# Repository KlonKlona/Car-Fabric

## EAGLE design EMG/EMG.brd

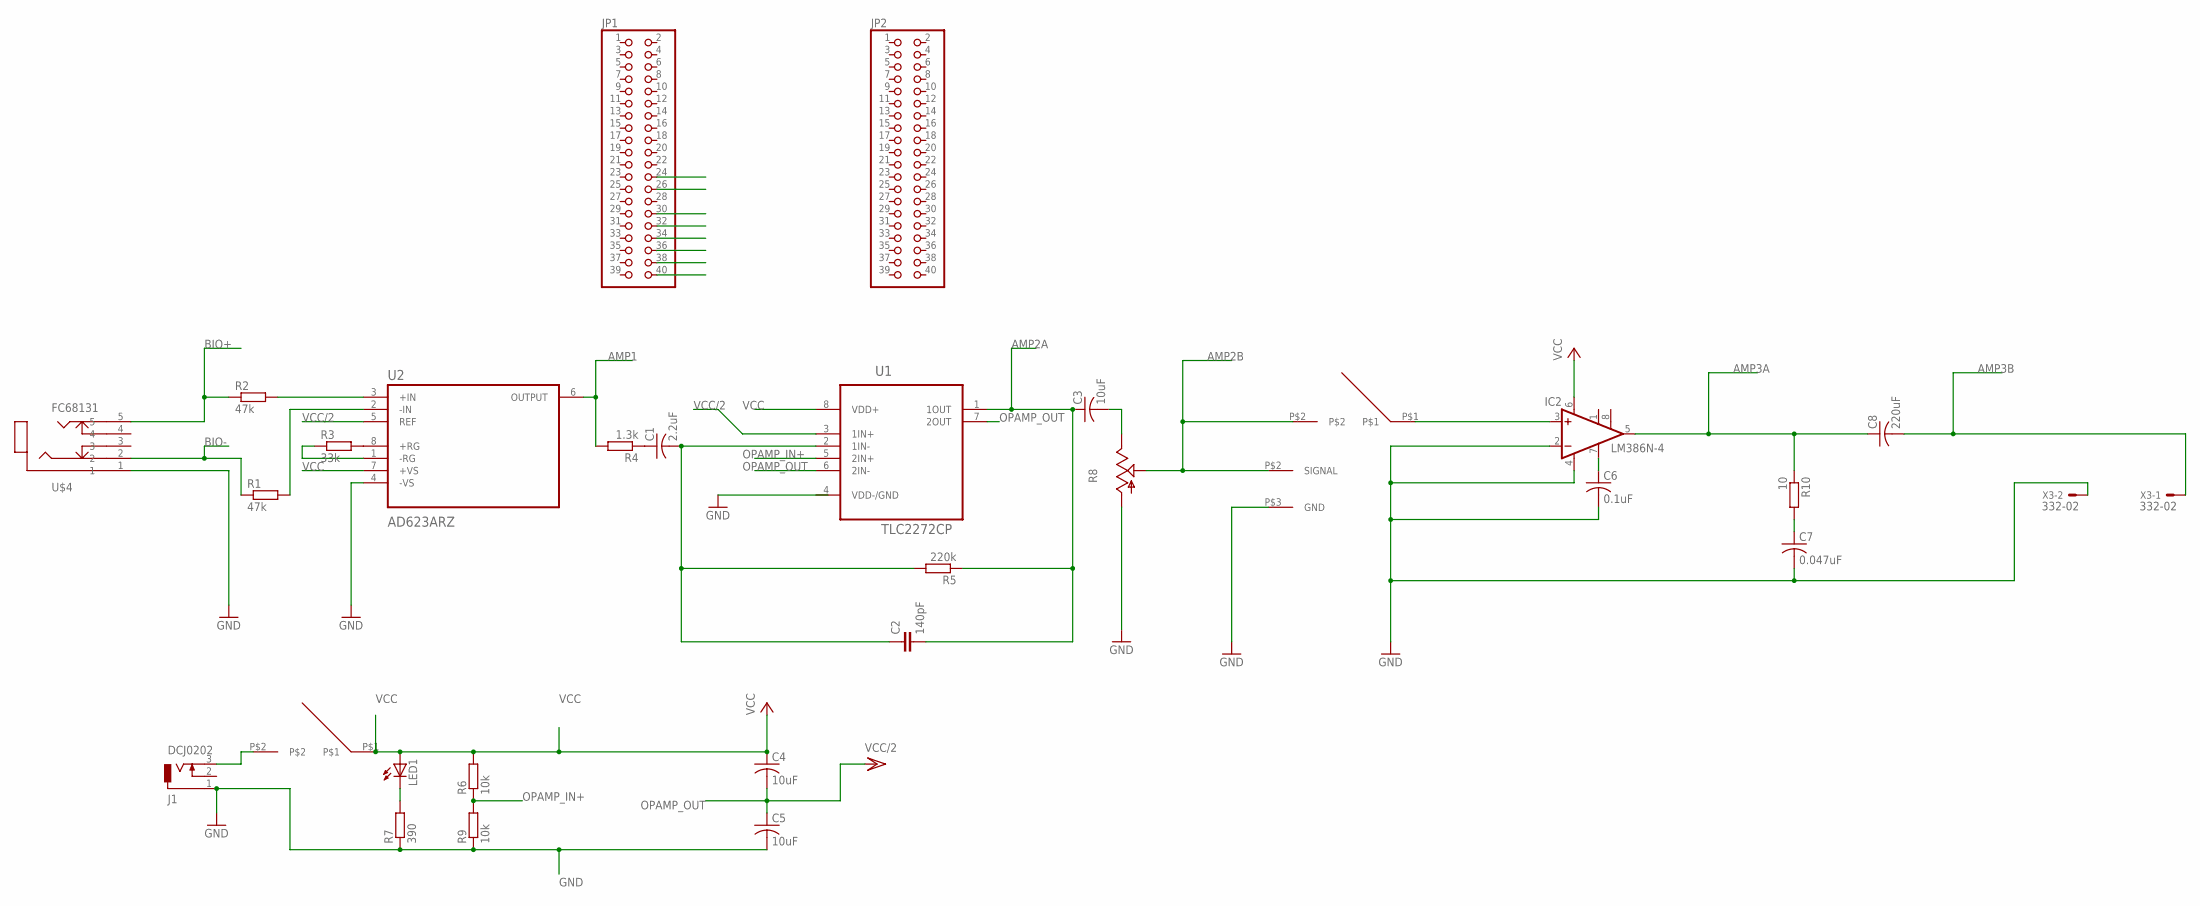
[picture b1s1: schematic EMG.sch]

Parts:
C1: 2.2uF; C025-025X050
C2: 140pF; C7.5B3
C3, C4, C5: 10uF; C025-025X050
C6: 0.1uF; C025-025X050
C7: 0.047uF; C050-030X075
C8: 220uF; C050-030X075
IC2: LM386N-4; DIL08
J1: DCJ0202
JP1, JP2: PINHD-2X20; 2X20
LED1: LED3MM
R1, R2: 47k; 0204/7
R3: 33k; 0204/7
R4: 1.3k; 0204/7
R5: 220k; 0204/7
R6, R9: 10k; 0204/7
R7: 390; 0204/7
R8: TRIM_US-B25U; B25U
R10: 10; 0204/7
U1: TLC2272CP; DIP254P762X508-8
U2: AD623ARZ; SOIC127P600X175-8N
U$1, U$2: CHL-706PG01LWB; PUSH_BUTTON
U$3: 1503_12_JACK_3,5
U$4: FC68131; FC68131-5P
X3: 332-02

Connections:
AMP1: JP1.34, R4.2, U2.6 (OUTPUT)
AMP2A: C2.2, C3.1, JP1.36, R5.1, U1.1 (1OUT)
AMP2B: JP1.38, R8.S, U$2.P$2, U$3.P$2 (SIGNAL)
AMP3A: C8.1, IC2.5 (OUT), R10.1
AMP3B: C8.2, JP1.40, X3.1
BIO+: JP1.32, R2.1, U$4.5
BIO-: JP1.30, R1.1, U$4.2
GND: C5.2, C6.2, C7.2, IC2.2 (-IN), IC2.4 (GND), J1.1, JP1.24, R7.1, R8.A, R9.1, U2.4 (-VS), U$3.P$3 (GND), U$4.1, X3.2
unnamed: R3.2, U2.8 (+RG)
unnamed: R3.1, U2.1 (-RG)
unnamed: R2.2, U2.3 (+IN)
unnamed: R1.2, U2.2 (-IN)
unnamed: C1.1, R4.1
unnamed: J1.3, U$1.P$2
unnamed: C1.2, C2.1, R5.2, U1.2 (1IN-)
unnamed: C3.2, R8.E
unnamed: C6.1, IC2.7 (BYPASS)
unnamed: IC2.3 (+IN), U$2.P$1
unnamed: LED1.K (C), R7.2
unnamed: C7.1, R10.2
OPAMP_IN+: R6.1, R9.2, U1.5 (2IN+)
OPAMP_OUT: C4.2, C5.1, U1.6 (2IN-), U1.7 (2OUT)
VCC: C4.1, IC2.6 (VS), JP1.26, LED1.A, R6.2, U1.8 (VDD+), U2.7 (+VS), U$1.P$1
VCC/2: U1.3 (1IN+), U2.5 (REF)

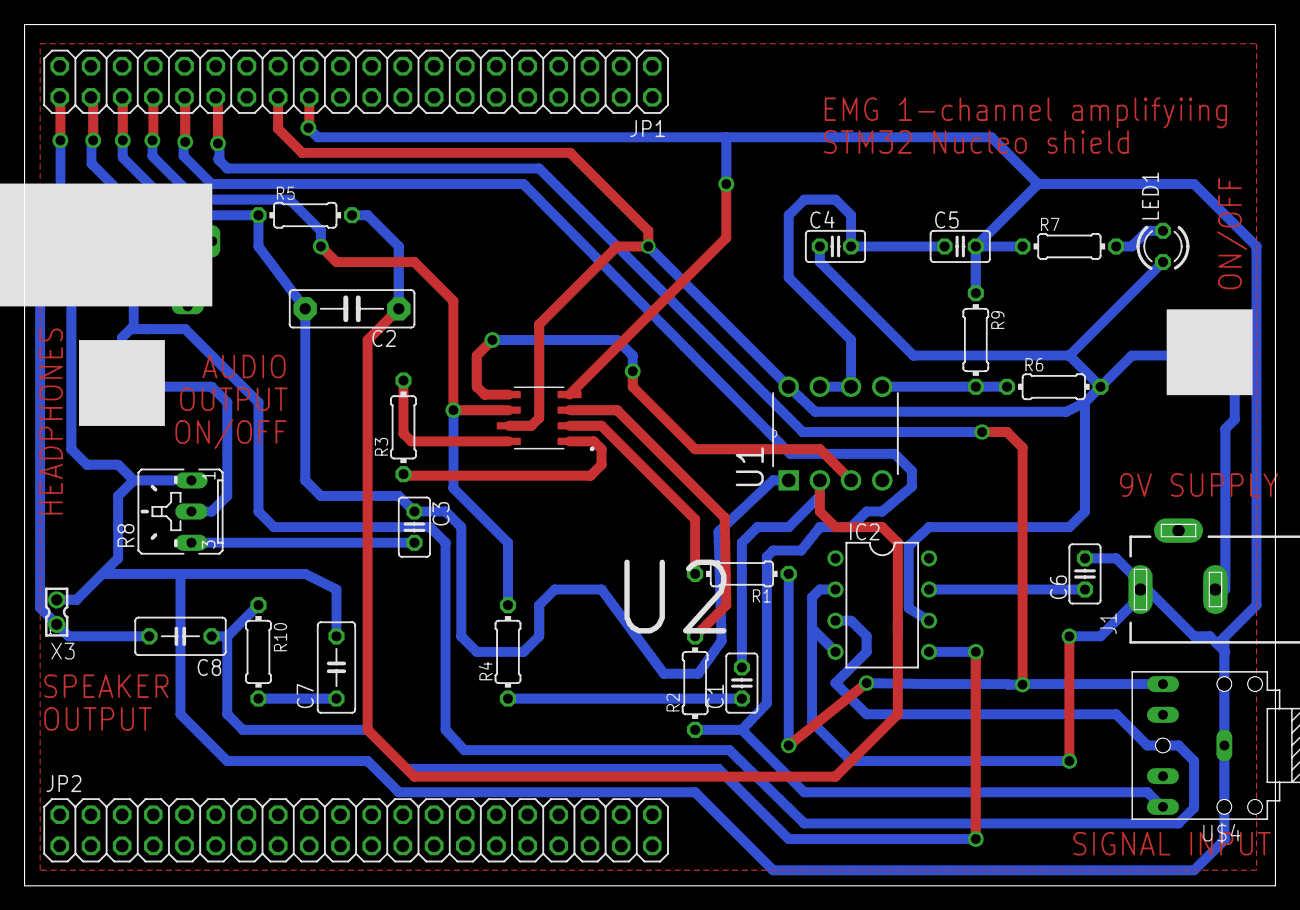
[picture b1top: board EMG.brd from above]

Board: 2 copper layers, 101.9 x 70.1 mm, 30 parts (0 on the bottom side), 24 nets.

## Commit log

2019-03-14 Trash
    Trash delete
